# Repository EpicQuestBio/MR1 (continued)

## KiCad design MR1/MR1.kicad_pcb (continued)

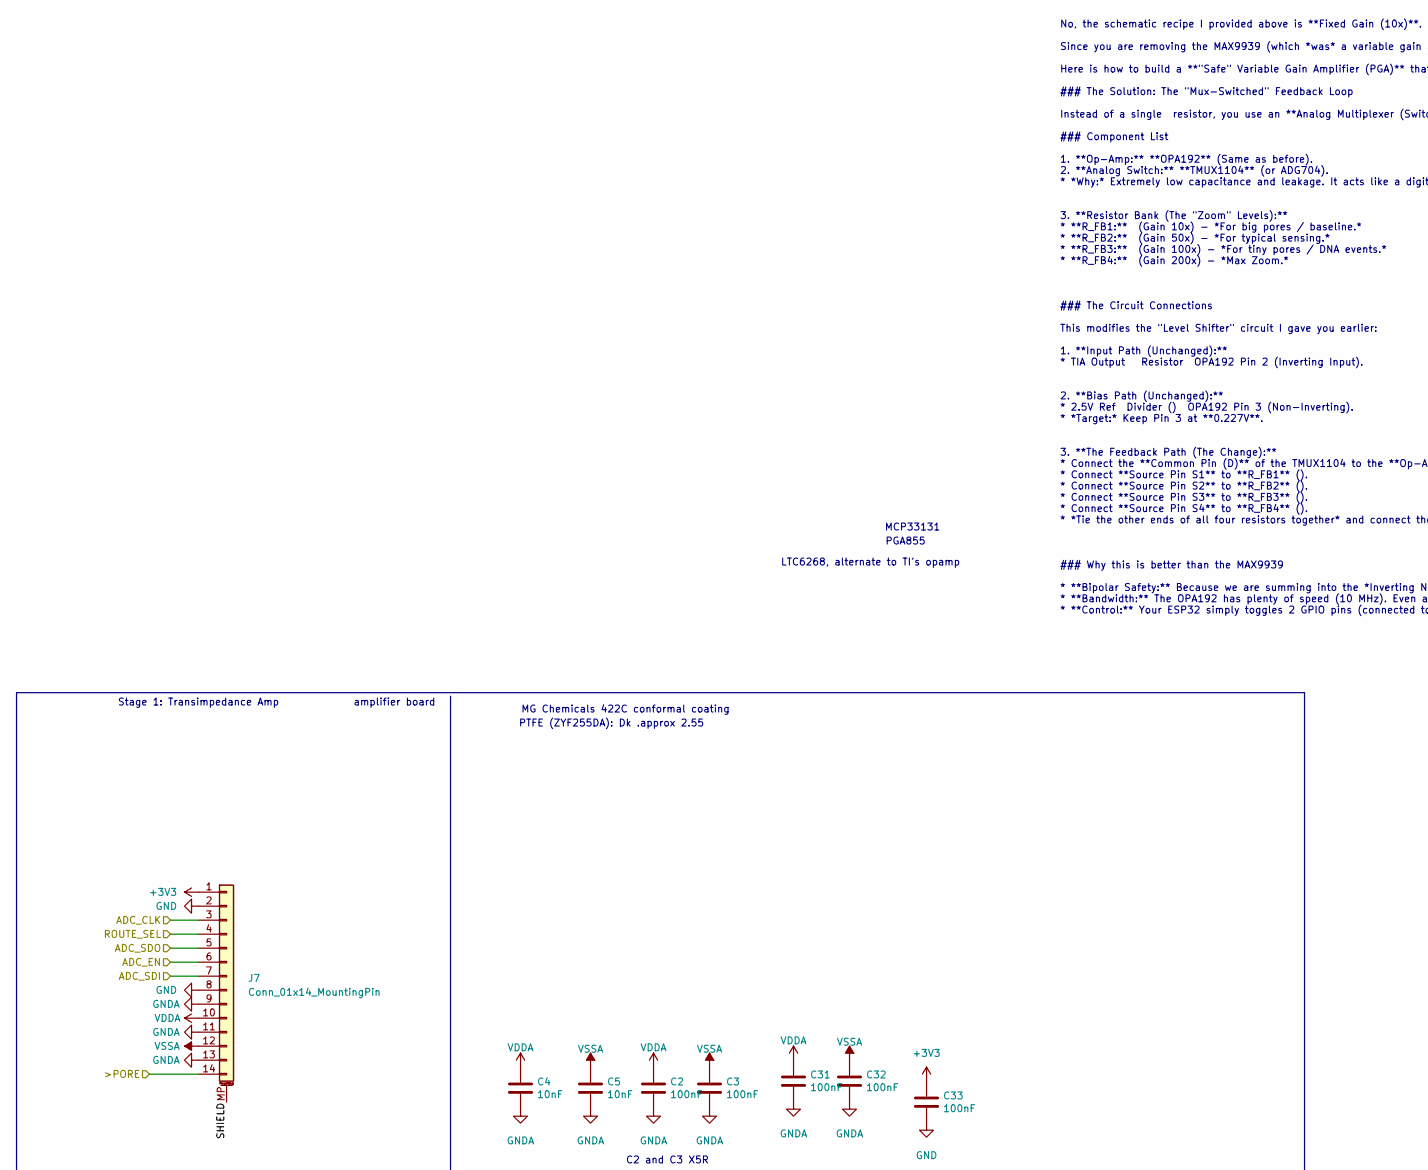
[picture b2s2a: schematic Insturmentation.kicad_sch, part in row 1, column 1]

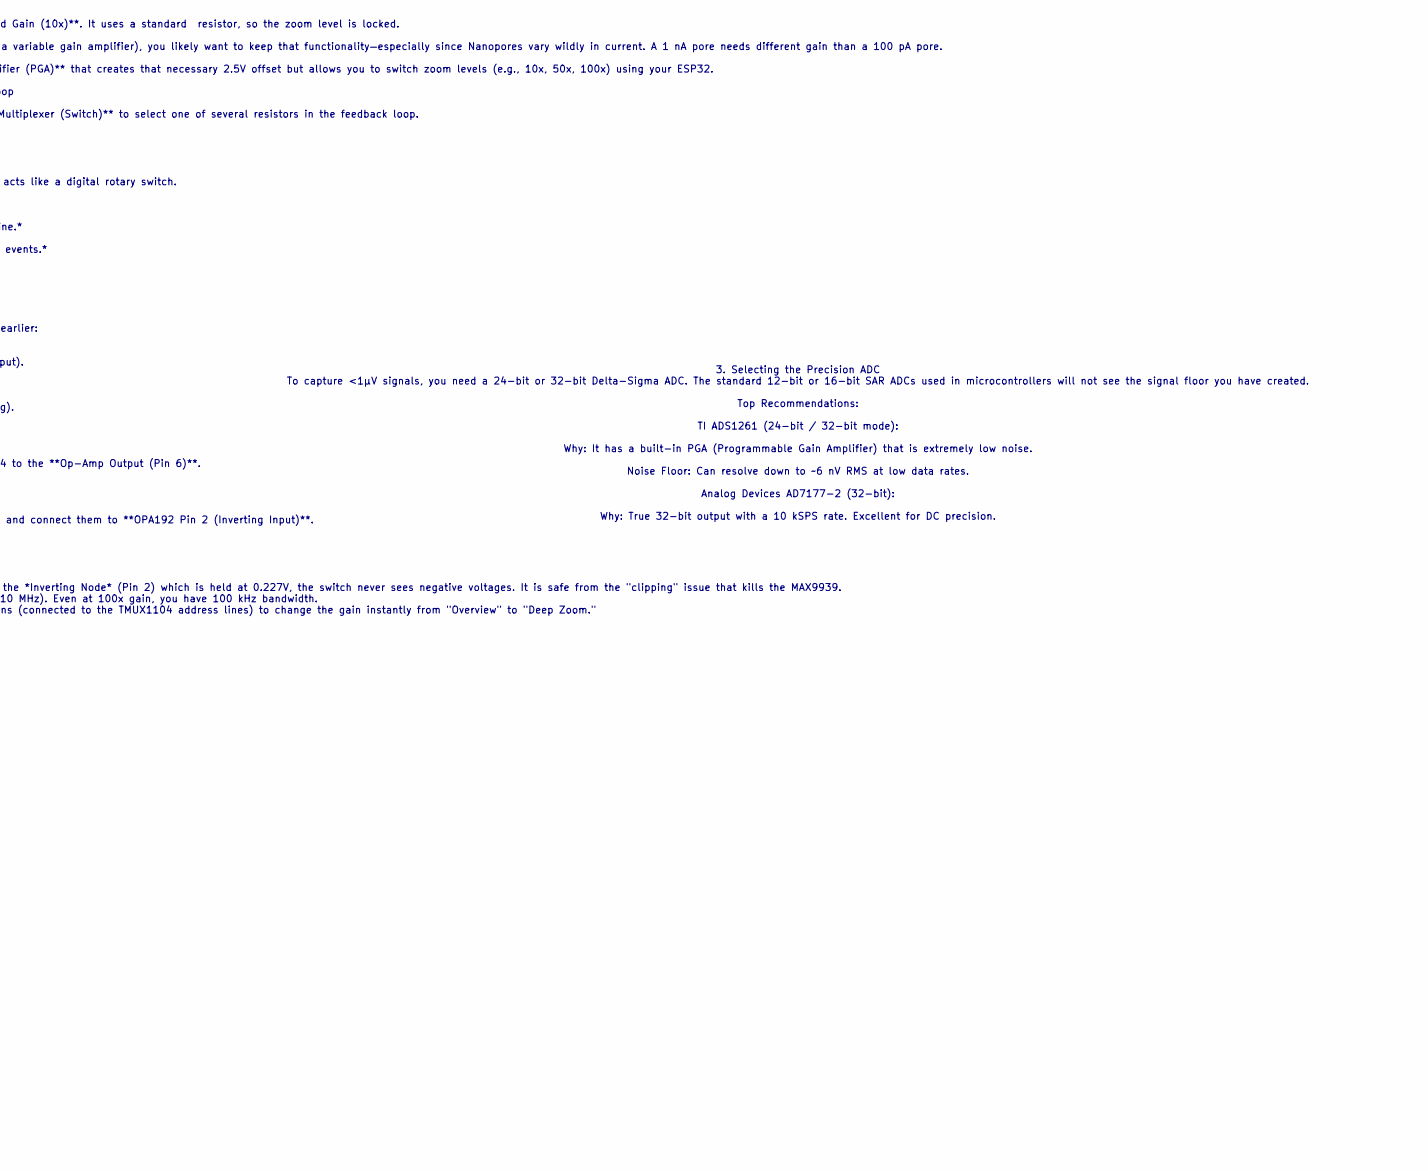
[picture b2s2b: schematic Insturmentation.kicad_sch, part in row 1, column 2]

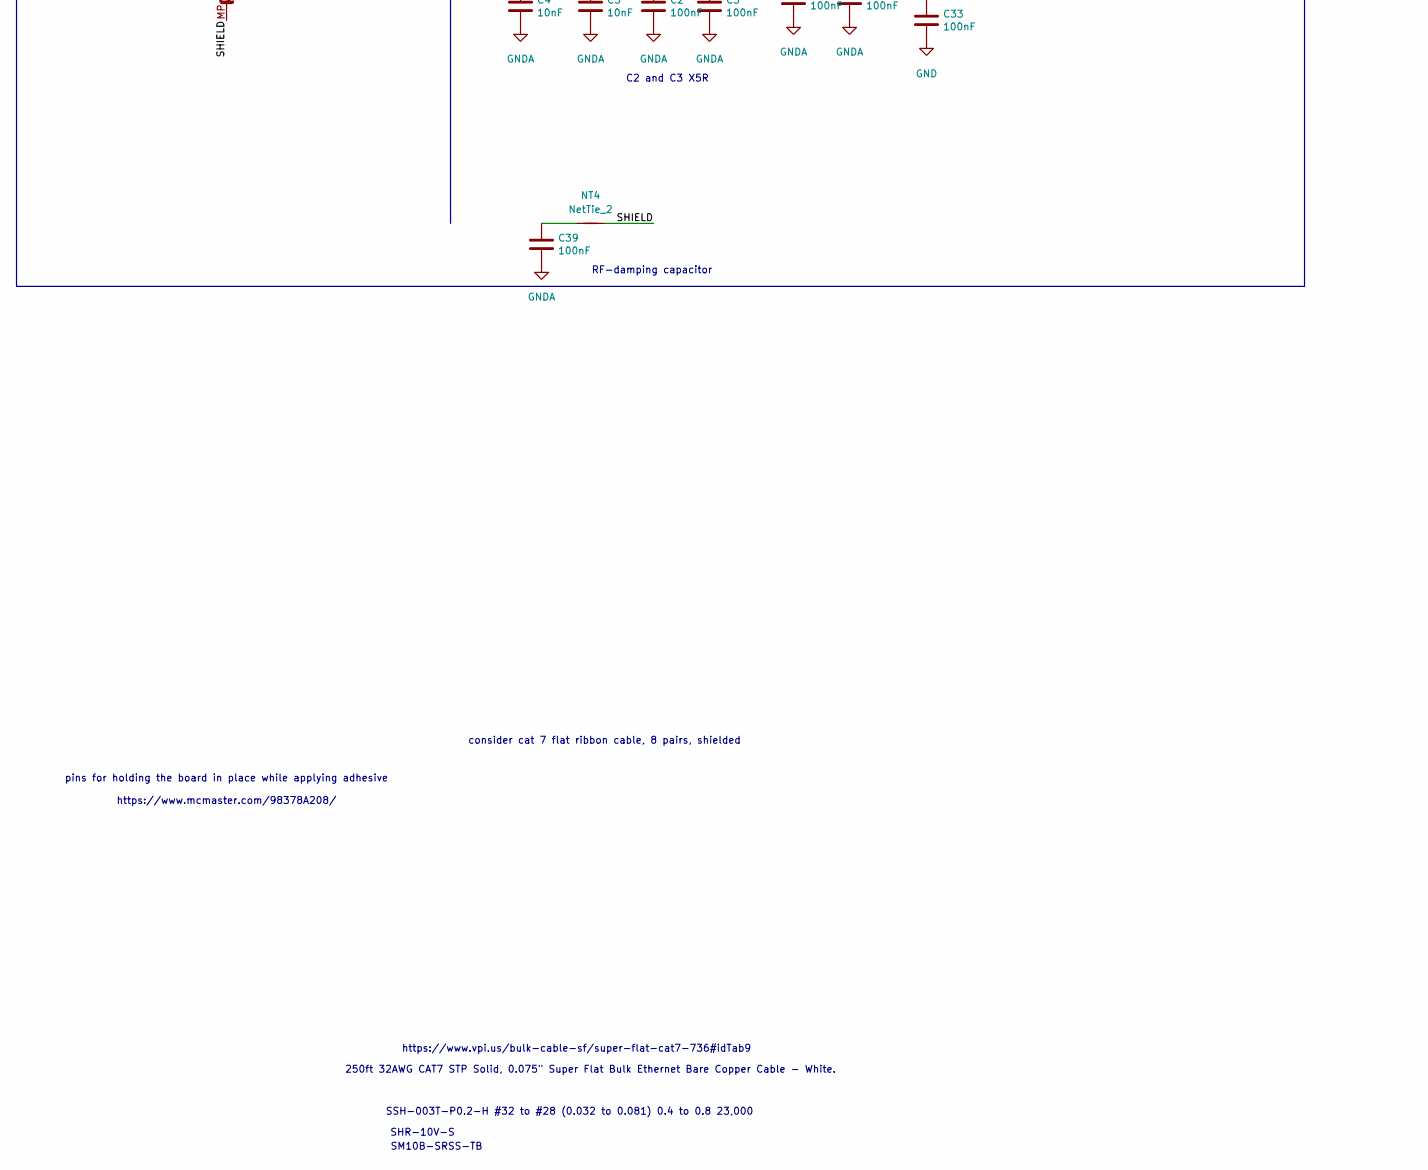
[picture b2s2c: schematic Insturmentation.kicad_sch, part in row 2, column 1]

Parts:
C2, C3, C31, C32, C33, C39: 100nF; C_0402_1005Metric; LCSC C15255
C4, C5: 10nF; C_0402_1005Metric; LCSC C1525
J7: Conn_01x14_MountingPin; Amphenol_F32R-1A7x1-11014_1x14-1MP_P0.5mm_Horizontal; LCSC C2856818
NT4: NetTie_2; NetTie-2_SMD_Pad0.5mm

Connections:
+3V3: C33.1, J7.1; also elsewhere on the board
/Ignition/>PORE: J7.14; also elsewhere on the board
/Insturmentation/ADC_CLK: J7.3; also elsewhere on the board
/Insturmentation/ADC_EN: J7.6; also elsewhere on the board
/Insturmentation/ADC_SDI: J7.7; also elsewhere on the board
/Insturmentation/ADC_SDO: J7.5; also elsewhere on the board
/Insturmentation/ROUTE_SEL: J7.4; also elsewhere on the board
/Insturmentation/SHIELD: J7.MP (MountPin), NT4.2
GND: C33.2, J7.2, J7.8; also elsewhere on the board
GNDA: C2.2, C3.2, C4.2, C5.2, C31.2, C32.2, C39.2, J7.9, J7.11, J7.13; also elsewhere on the board
unnamed: C39.1, NT4.1
VDDA: C2.1, C4.1, C31.1, J7.10; also elsewhere on the board
VSSA: C3.1, C5.1, C32.1, J7.12; also elsewhere on the board

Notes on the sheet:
consider cat 7 flat ribbon cable, 8 pairs, shielded
pins for holding the board in place while applying adhesive https://www.mcmaster.com/98378A208/
C2 and C3 X5R
PGA855
https://www.vpi.us/bulk-cable-sf/super-flat-cat7-736#idTab9
SM10B-SRSS-TB
PTFE (ZYF255DA): Dk .approx 2.55
amplifier board
No, the schematic recipe I provided above is **Fixed Gain (10x)**. It uses a standard resistor, so the zoom level is locked. Since you are removing the MAX9939 (which *was* a variable gain amplifier), you likely want to keep that functionality—especially since Nanopores vary wildly in current. A 1 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
Stage 1: Transimpedance Amp
MCP33131
MG Chemicals 422C conformal coating
250ft 32AWG CAT7 STP Solid, 0.075" Super Flat Bulk Ethernet Bare Copper Cable - White.
SHR-10V-S
LTC6268, alternate to TI's opamp
RF-damping capacitor
SSH-003T-P0.2-H #32 to #28 (0.032 to 0.081) 0.4 to 0.8 23,000
3. Selecting the Precision ADC To capture <1µV signals, you need a 24-bit or 32-bit Delta-Sigma ADC. The standard 12-bit or 16-bit SAR ADCs used in microcontrollers will not see the signal floor you have created. Top Recommendations: TI ADS1261 (24-bit / 32-bit mode): Why: It has a built-in PGA (Pr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

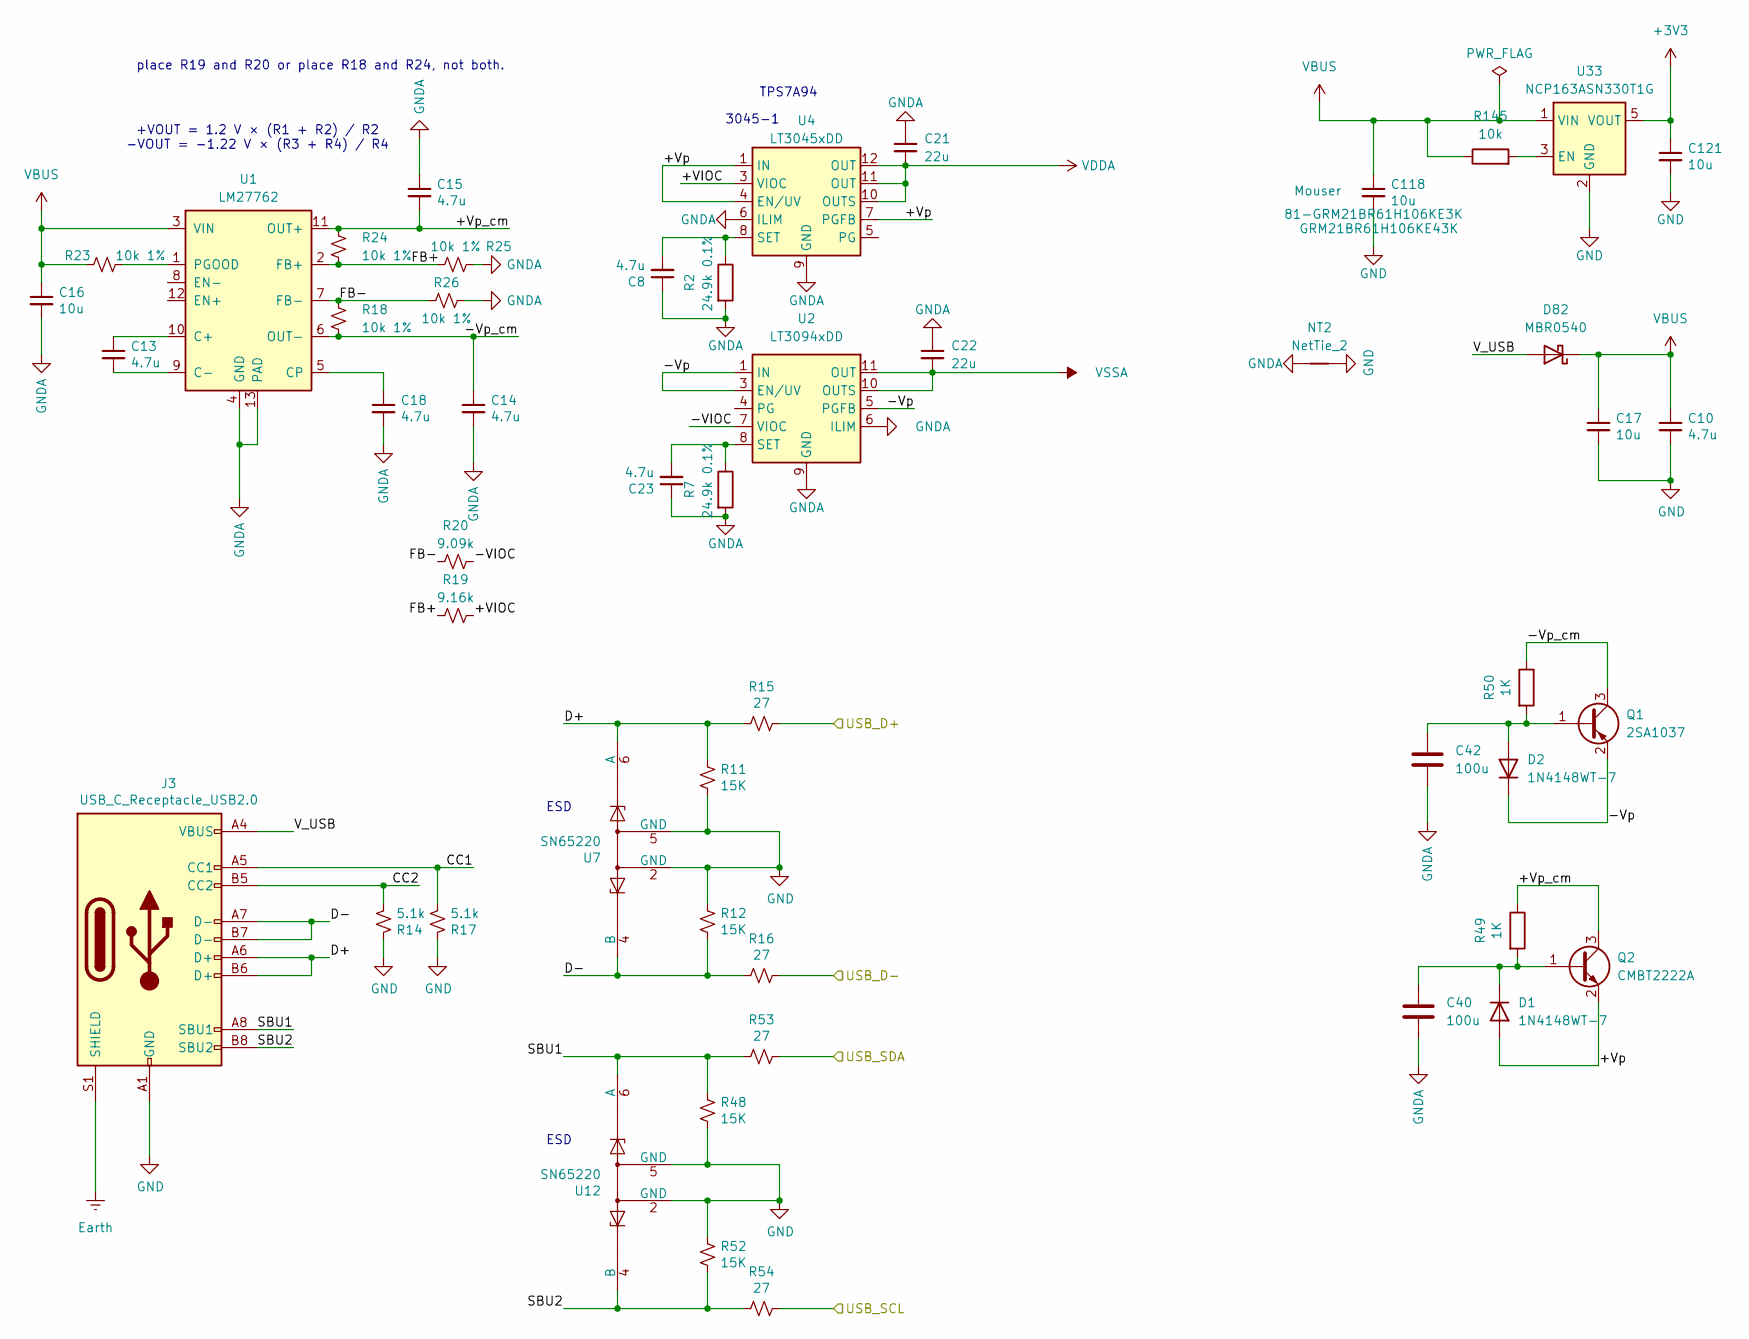
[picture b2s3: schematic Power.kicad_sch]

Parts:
C8, C10, C13, C14, C15, C18, C23: 4.7u; C_0402_1005Metric; Manufacturer_Part_Number JMK107C6475KA-T; LCSC C19702
C16, C17: 10u; C_0402_1005Metric; Manufacturer_Part_Number LMK212ABJ106MG-T; LCSC C1713
C21, C22: 22u; C_0402_1005Metric; MPN GRM21BR61H106KE43K; LCSC C23737
C40, C42: 100u; C_1206_3216Metric; LCSC C15008
C118, C121: 10u; C_0402_1005Metric; MPN GRM21BR61H106KE43K; LCSC C1713
D1, D2: 1N4148WT-7; D_SOD-523; LCSC C107849
D82: MBR0540; D_SOD-123; MPN MBR0540L-TP; LCSC C5204747
J3: USB_C_Receptacle_USB2.0; USB_C_Receptacle_HRO_TYPE-C-31-M-12; Manufacturer_Part_Number USB4105-GF-A; LCSC C165948
NT2: NetTie_2; NetTie-2_SMD_Pad0.5mm
Q1: 2SA1037; SOT-23; LCSC C14902
Q2: CMBT2222A; SOT-23; LCSC C2152
R2, R7: 24.9k 0.1%; R_0402_1005Metric; LCSC C25327
R11, R12, R48, R52: 15K; R_0402_1005Metric; Manufacturer_Part_Number RC0603FR-1315KL; LCSC C25275
R14, R17: 5.1k; R_0402_1005Metric; Manufacturer_Part_Number CR0603-FX-5101ELF; LCSC C25212
R15, R16, R53, R54: 27; R_0402_1005Metric; Manufacturer_Part_Number RK73B1JTTDD270J; LCSC C25078
R18, R23, R24, R25, R26: 10k 1%; R_0402_1005Metric; MPN RK73H1ETTPB1002F; LCSC C60490
R19: 9.16k; R_0402_1005Metric; MPN RK73H1ETTPB1002F; LCSC C25991
R20: 9.09k; R_0402_1005Metric; MPN RK73H1ETTPB1002F; LCSC C25879
R49, R50: 1K; R_0402_1005Metric; LCSC C25149
R145: 10k; R_0402_1005Metric; MPN RK73H1ETTPB1002F; LCSC C60490
U1: LM27762; WSON-12-1EP_3x2mm_P0.5mm_EP1x2.65_ThermalVias; MPN LM27762DSSR; LCSC C473398
U2: LT3094xDD; DFN-12-1EP_3x3mm_P0.45mm_EP1.65x2.38mm_ThermalVias; LCSC C670493
U4: LT3045xDD; DFN-12-1EP_3x3mm_P0.5mm_EP1.6x2.5mm; MPN LT3045EDD-1#TRPBF; LCSC C514420
U7, U12: SN65220; SOT-23-6; Manufacturer_Part_Number SN65220DBVT; LCSC C21787
U33: NCP163ASN330T1G; SOT-23-5; MPN NCP114ASN330T1G; LCSC C156285

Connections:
+3V3: C121.1, U33.5 (VOUT); also elsewhere on the board
/Microcontroller/GPIO19: R16.2; also elsewhere on the board
/Microcontroller/GPIO20: R15.2; also elsewhere on the board
/Microcontroller/GPIO21: R53.2; also elsewhere on the board
/Microcontroller/GPIO26: R54.2; also elsewhere on the board
/Power/+VIOC: R19.1, U4.3 (VIOC)
/Power/+Vp: D1.2 (A), Q2.2 (E), U4.1 (IN), U4.2 (IN), U4.4 (EN/UV), U4.7 (PGFB)
/Power/+Vp_cm: C15.2, Q2.3 (C), R24.2, R49.1, U1.11 (OUT+)
/Power/-VIOC: R20.1, U2.7 (VIOC)
/Power/-Vp: D2.1 (K), Q1.2 (E), U2.1 (IN), U2.2 (IN), U2.3 (EN/UV), U2.5 (PGFB), U2.13 (IN)
/Power/-Vp_cm: C14.1, Q1.3 (C), R18.1, R50.1, U1.6 (OUT-)
/Power/CC1: J3.A5 (CC1), R17.2
/Power/CC2: J3.B5 (CC2), R14.2
/Power/D+: J3.A6 (D+), J3.B6 (D+), R11.1, R15.1, U7.1, U7.6 (A)
/Power/D-: J3.A7 (D-), J3.B7 (D-), R12.2, R16.1, U7.3, U7.4 (B)
/Power/FB+: R19.2, R24.1, R25.2, U1.2 (FB+)
/Power/FB-: R18.2, R20.2, R26.1, U1.7 (FB-)
/Power/SBU1: J3.A8 (SBU1), R48.1, R53.1, U12.1, U12.6 (A)
/Power/SBU2: J3.B8 (SBU2), R52.2, R54.1, U12.3, U12.4 (B)
/Power/V_USB: D82.2 (A), J3.A4 (VBUS), J3.A9 (VBUS), J3.B4 (VBUS), J3.B9 (VBUS)
Earth: J3.S1 (SHIELD); also elsewhere on the board
GND: C10.2, C17.2, C118.2, C121.2, J3.A1 (GND), J3.A12 (GND), J3.B1 (GND), J3.B12 (GND), NT2.2, R11.2, R12.1, R14.1, R17.1, R48.2, R52.1, U7.2 (GND), U7.5 (GND), U12.2 (GND), U12.5 (GND), U33.2 (GND); also elsewhere on the board
GNDA: C8.1, C14.2, C15.1, C16.2, C18.2, C21.1, C22.1, C23.1, C40.2, C42.1, NT2.1, R2.2, R7.2, R25.1, R26.2, U1.4 (GND), U1.13 (PAD), U2.6 (ILIM), U2.9 (GND), U4.6 (ILIM), U4.9 (GND), U4.13 (GND); also elsewhere on the board
unnamed: C40.1, D1.1 (K), Q2.1 (B), R49.2
unnamed: C42.2, D2.2 (A), Q1.1 (B), R50.2
unnamed: C13.1, U1.10 (C+)
unnamed: C13.2, U1.9 (C-)
unnamed: C18.1, U1.5 (CP)
unnamed: R23.2, U1.1 (PGOOD)
unnamed: C23.2, R7.1, U2.8 (SET)
unnamed: C8.2, R2.1, U4.8 (SET)
unnamed: R145.2, U33.3 (EN)
VBUS: C10.1, C16.1, C17.1, C118.1, D82.1 (K), R23.1, R145.1, U1.3 (VIN), U33.1 (VIN)
VDDA: C21.2, U4.10 (OUTS), U4.11 (OUT), U4.12 (OUT); also elsewhere on the board
VSSA: C22.2, U2.10 (OUTS), U2.11 (OUT), U2.12 (OUT); also elsewhere on the board

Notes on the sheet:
ESD
+VOUT = 1.2 V × (R1 + R2) / R2 -VOUT = -1.22 V × (R3 + R4) / R4
3045-1
TPS7A94
place R19 and R20 or place R18 and R24, not both.

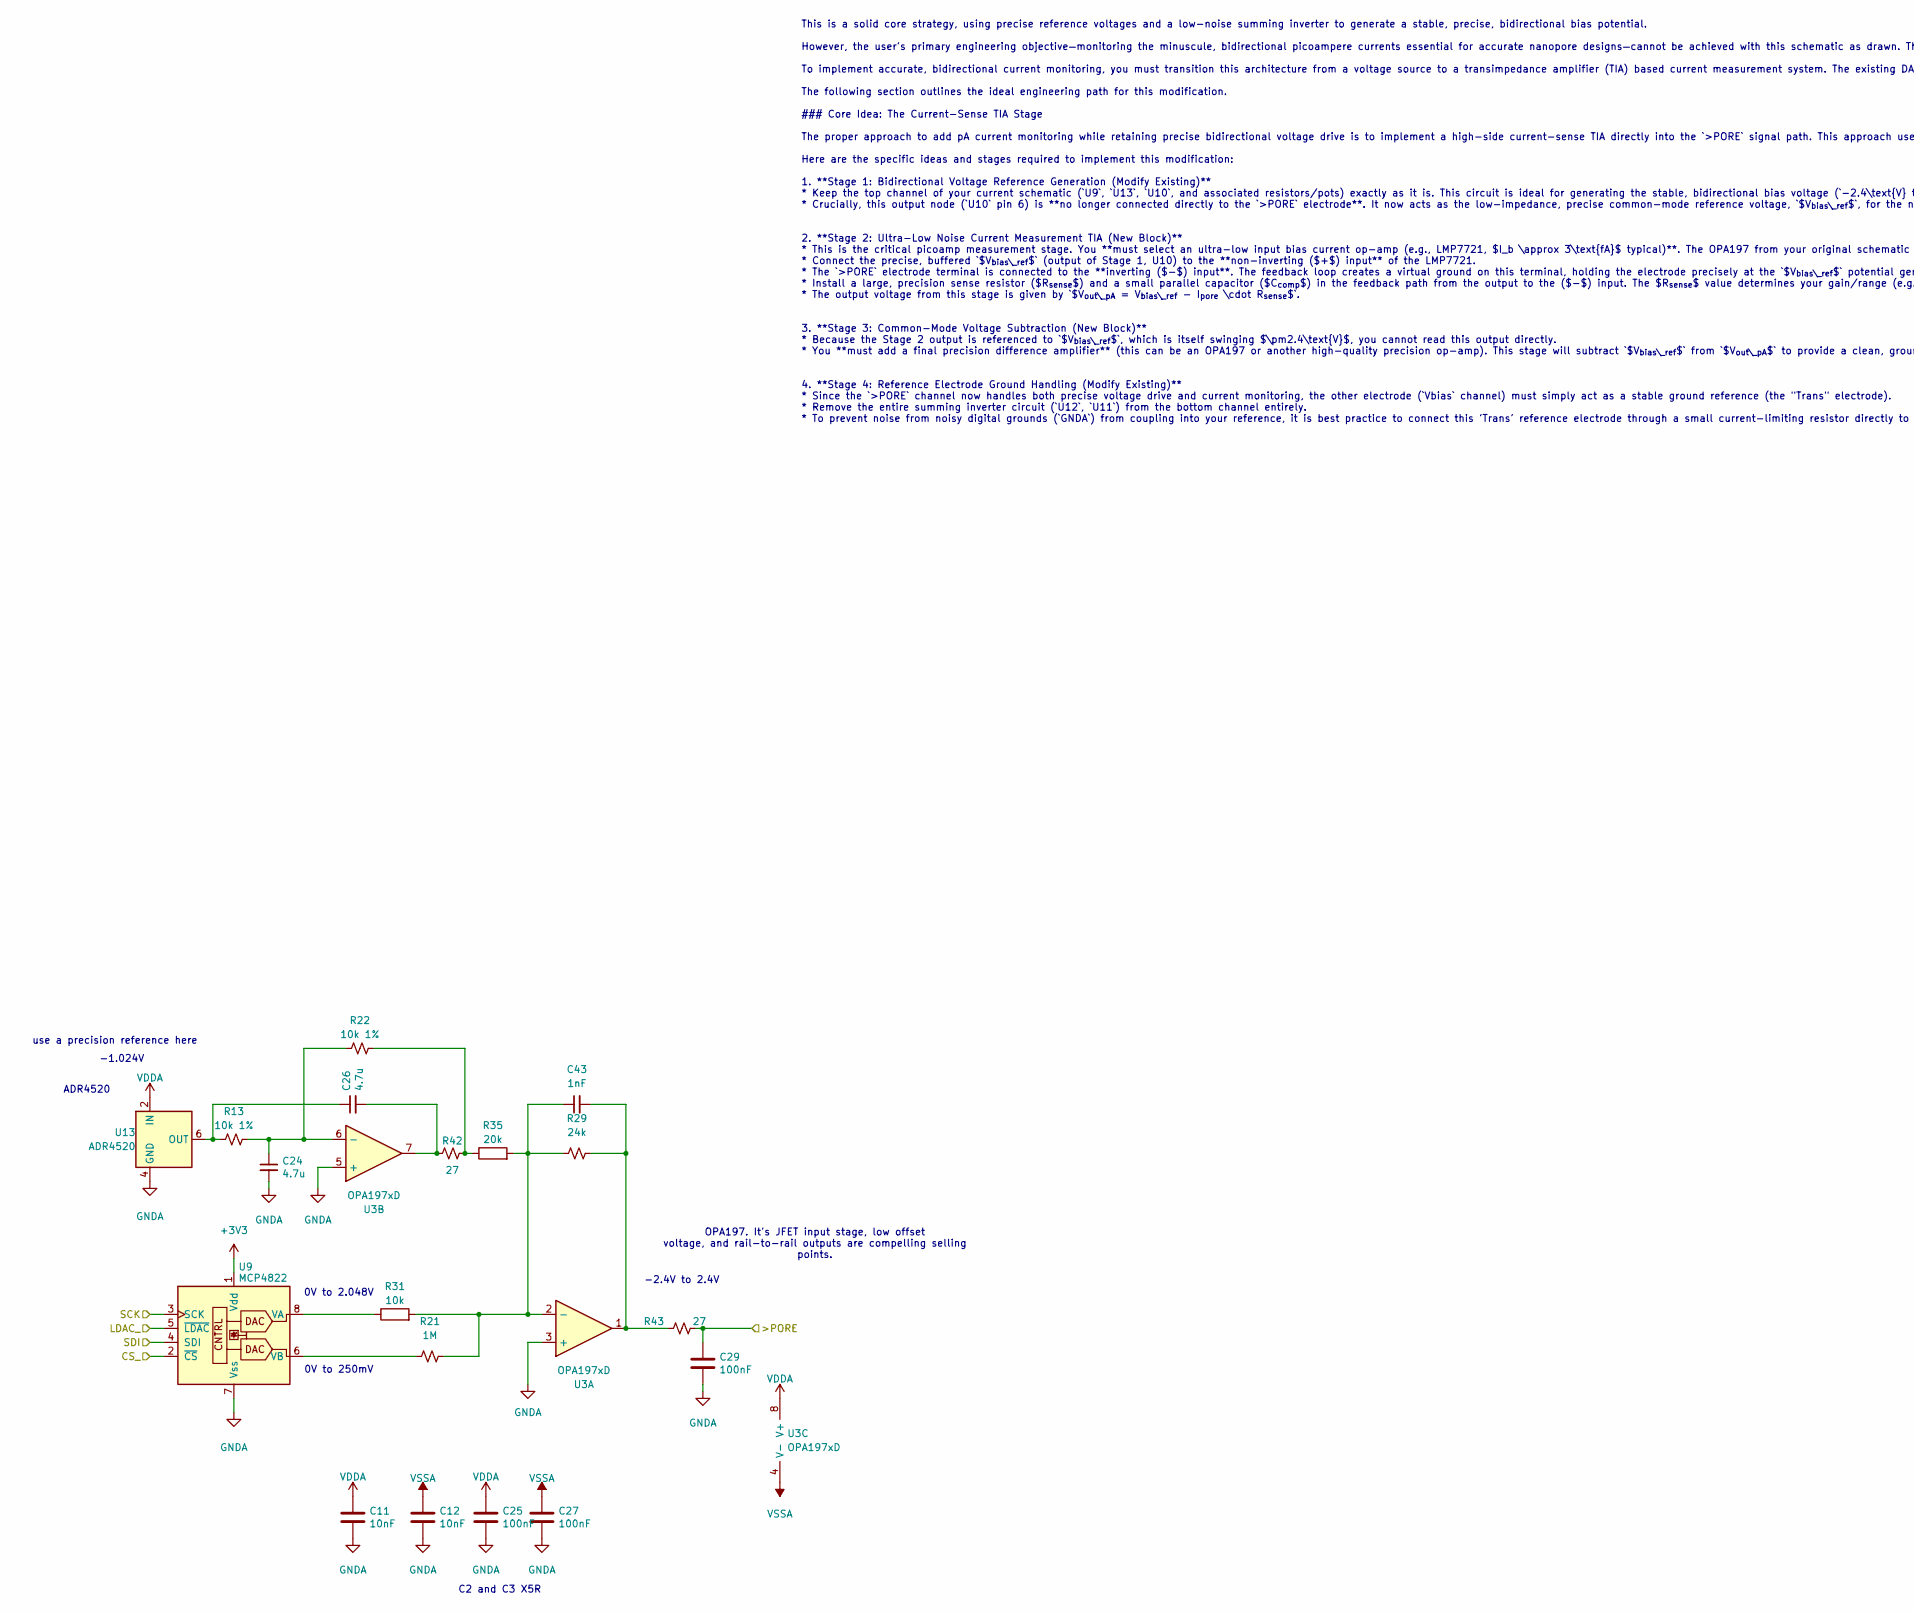
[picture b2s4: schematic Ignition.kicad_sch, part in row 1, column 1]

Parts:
C11, C12: 10nF; C_0402_1005Metric; LCSC C1525
C24, C26: 4.7u; C_0402_1005Metric; Manufacturer_Part_Number JMK107C6475KA-T; LCSC C19702
C25, C27, C29: 100nF; C_0402_1005Metric; LCSC C15255
C43: 1nF; C_0402_1005Metric; LCSC C1523
R13, R22: 10k 1%; R_0402_1005Metric; MPN RK73H1ETTPB1002F; LCSC C60490
R21: 1M; R_0402_1005Metric; MPN RK73H1ETTPB1002F; LCSC C25488
R29: 24k; R_0402_1005Metric; MPN RK73H1ETTPB1002F; LCSC C25324
R31: 10k; R_0402_1005Metric; LCSC C60490
R35: 20k; R_0402_1005Metric; LCSC C25310
R42, R43: 27; R_0402_1005Metric; MPN RC0402JR-0727RL; LCSC C25078
U3: OPA197xD; VSSOP-8_3x3mm_P0.65mm; MPN OPA197IDGKT; LCSC C133554
U9: MCP4822; SOIC-8-1EP_3.9x4.9mm_P1.27mm_EP2.29x3mm; MPN MCP4822T-E/SN; LCSC C16040
U13: ADR4520; SOIC-8_3.9x4.9mm_P1.27mm; MPN ADR4520ARZ-R7; LCSC C659578

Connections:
+3V3: U9.1 (Vdd); also elsewhere on the board
/Ignition/>PORE: C29.1, R43.2; also elsewhere on the board
/Ignition/CS_: U9.2 (~CS); also elsewhere on the board
/Ignition/LDAC_: U9.5 (~LDAC); also elsewhere on the board
/Ignition/SCK: U9.3 (SCK); also elsewhere on the board
/Ignition/SDI: U9.4 (SDI); also elsewhere on the board
GNDA: C11.2, C12.2, C24.2, C25.2, C27.2, C29.2, U3.3 (+), U3.5 (+), U9.7 (Vss), U13.4 (GND); also elsewhere on the board
unnamed: C26.2, R42.1, U3.7
unnamed: C43.2, R29.1, R43.1, U3.1
unnamed: R22.1, R35.1, R42.2
unnamed: C43.1, R21.1, R29.2, R31.2, R35.2, U3.2 (-)
unnamed: C24.1, R13.1, R22.2, U3.6 (-)
unnamed: R31.1, U9.8 (VA)
unnamed: R21.2, U9.6 (VB)
unnamed: C26.1, R13.2, U13.6 (OUT)
VDDA: C11.1, C25.1, U3.8 (V+), U13.2 (IN); also elsewhere on the board
VSSA: C12.1, C27.1, U3.4 (V-); also elsewhere on the board

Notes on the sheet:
use a precision reference here
This is a solid core strategy, using precise reference voltages and a low-noise summing inverter to generate a stable, precise, bidirectional bias potential. However, the user's primary engineering objective—monitoring the minuscule, bidirectional picoampere currents essential for accurate nanopore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
0V to 250mV
C2 and C3 X5R
-2.4V to 2.4V
OPA197. It's JFET input stage, low offset voltage, and rail-to-rail outputs are compelling selling points.
ADR4520
0V to 2.048V
-1.024V

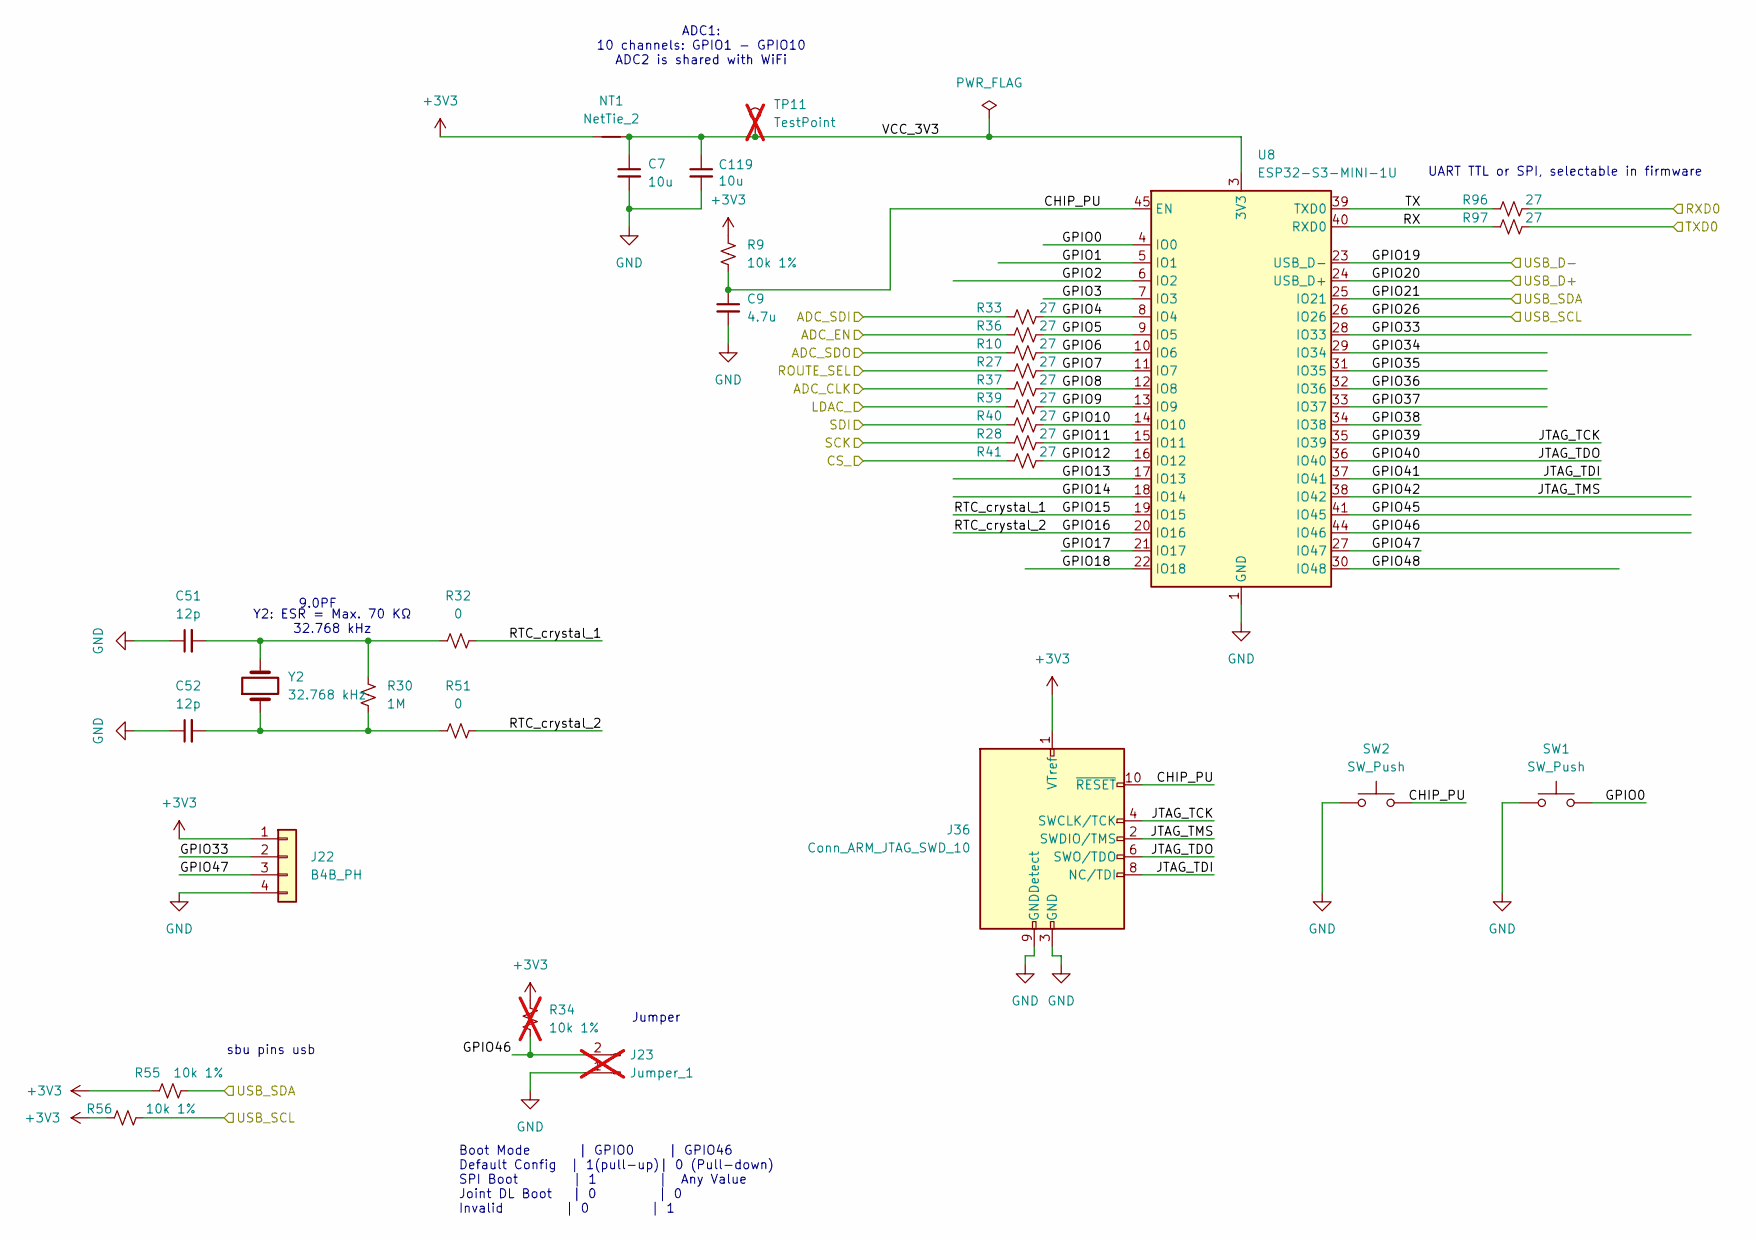
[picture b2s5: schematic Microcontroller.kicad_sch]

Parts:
C7, C119: 10u; C_0402_1005Metric; MPN GRM21BR61H106KE43K; LCSC C1713
C9: 4.7u; C_0402_1005Metric; MPN LMK107BJ475KA-T; LCSC C19702
C51, C52: 12p; C_0402_1005Metric; MPN 0402YA120JAT2A; LCSC C1550
J22: B4B_PH; JST_PH_B4B-PH-K_1x04_P2.00mm_Vertical; MPN B4B-PH-K-S; LCSC C131334
J23: Jumper_1; PinHeader_1x02_P2.54mm_Vertical; LCSC C492401; not fitted
J36: Conn_ARM_JTAG_SWD_10; PinHeader_2x05_P1.27mm_Vertical_SMD; MPN FTSH-105-01-F-DV-007-P-TR; LCSC C521634
NT1: NetTie_2; NetTie-2_SMD_Pad0.5mm
R9, R55, R56: 10k 1%; R_0402_1005Metric; MPN RK73H1ETTPB1002F; LCSC C60490
R10, R27, R28, R33, R36, R37, R39, R40, R41, R96, R97: 27; R_0402_1005Metric; MPN RC0402JR-0727RL; LCSC C25078
R30: 1M; R_0402_1005Metric; MPN CRCW04021M00DHEDP; LCSC C25488
R32, R51: 0; R_0402_1005Metric; MPN CRCW04020000Z0EDC; LCSC C25740
R34: 10k 1%; R_0402_1005Metric; MPN RK73H1ETTPB1002F; LCSC C60490; not fitted
SW1, SW2: SW_Push; SW_SPST_6mm_gull wing; MPN TS04-66-43-BK-160-SMT; LCSC C481177
TP11: TestPoint; TestPoint_Pad_D1.0mm; not fitted
U8: ESP32-S3-MINI-1U; ESP32-S2-MINI-1U; MPN ESP32-S3-MINI-1U-N8; LCSC C2980299
Y2: 32.768 kHz; Crystal_SMD_3215-2Pin_3.2x1.5mm; MPN FC3215AN 32.768K-90NN60KC5; LCSC C91275

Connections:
+3V3: J22.1, J36.1 (VTref), NT1.1, R9.1, R34.1, R55.1, R56.2; also elsewhere on the board
/Ignition/CS_: R41.1; also elsewhere on the board
/Ignition/LDAC_: R39.1; also elsewhere on the board
/Ignition/SCK: R28.1; also elsewhere on the board
/Ignition/SDI: R40.1; also elsewhere on the board
/Insturmentation/ADC_CLK: R37.1; also elsewhere on the board
/Insturmentation/ADC_EN: R36.1; also elsewhere on the board
/Insturmentation/ADC_SDI: R33.1; also elsewhere on the board
/Insturmentation/ADC_SDO: R10.1; also elsewhere on the board
/Insturmentation/ROUTE_SEL: R27.1; also elsewhere on the board
/Microcontroller/CHIP_PU: C9.1, J36.10 (~RESET), R9.2, SW2.2, U8.45 (EN)
/Microcontroller/GPIO0: SW1.2, U8.4 (IO0)
/Microcontroller/GPIO1: U8.5 (IO1)
/Microcontroller/GPIO2: U8.6 (IO2)
/Microcontroller/GPIO3: U8.7 (IO3)
/Microcontroller/GPIO4: R33.2, U8.8 (IO4)
/Microcontroller/GPIO5: R36.2, U8.9 (IO5)
/Microcontroller/GPIO6: R10.2, U8.10 (IO6)
/Microcontroller/GPIO7: R27.2, U8.11 (IO7)
/Microcontroller/GPIO8: R37.2, U8.12 (IO8)
/Microcontroller/GPIO9: R39.2, U8.13 (IO9)
/Microcontroller/GPIO10: R40.2, U8.14 (IO10)
/Microcontroller/GPIO11: R28.2, U8.15 (IO11)
/Microcontroller/GPIO12: R41.2, U8.16 (IO12)
/Microcontroller/GPIO13: U8.17 (IO13)
/Microcontroller/GPIO14: U8.18 (IO14)
/Microcontroller/GPIO15: R32.2, U8.19 (IO15)
/Microcontroller/GPIO16: R51.1, U8.20 (IO16)
/Microcontroller/GPIO17: U8.21 (IO17)
/Microcontroller/GPIO18: U8.22 (IO18)
/Microcontroller/GPIO19: U8.23 (USB_D-); also elsewhere on the board
/Microcontroller/GPIO20: U8.24 (USB_D+); also elsewhere on the board
/Microcontroller/GPIO21: R55.2, U8.25 (IO21); also elsewhere on the board
/Microcontroller/GPIO26: R56.1, U8.26 (IO26); also elsewhere on the board
/Microcontroller/GPIO33: J22.2, U8.28 (IO33)
/Microcontroller/GPIO34: U8.29 (IO34)
/Microcontroller/GPIO35: U8.31 (IO35)
/Microcontroller/GPIO36: U8.32 (IO36)
/Microcontroller/GPIO37: U8.33 (IO37)
/Microcontroller/GPIO38: U8.34 (IO38)
/Microcontroller/GPIO39: J36.4 (SWCLK/TCK), U8.35 (IO39)
/Microcontroller/GPIO40: J36.6 (SWO/TDO), U8.36 (IO40)
/Microcontroller/GPIO41: J36.8 (NC/TDI), U8.37 (IO41)
/Microcontroller/GPIO42: J36.2 (SWDIO/TMS), U8.38 (IO42)
/Microcontroller/GPIO45: U8.41 (IO45)
/Microcontroller/GPIO46: J23.2, R34.2, U8.44 (IO46)
/Microcontroller/GPIO47: J22.3, U8.27 (IO47)
/Microcontroller/GPIO48: U8.30 (IO48)
/Microcontroller/RX: R97.1, U8.40 (RXD0)
/Microcontroller/RXD0: R96.2
/Microcontroller/TX: R96.1, U8.39 (TXD0)
/Microcontroller/TXD0: R97.2
/Microcontroller/VCC_3V3: C7.1, C119.1, NT1.2, TP11.1 (1_1), U8.3 (3V3)
GND: C7.2, C9.2, C51.1, C52.1, C119.2, J22.4, J23.1, J36.3 (GND), J36.5 (GND), J36.9 (GNDDetect), SW1.1, SW2.1, U8.1 (GND), U8.2 (GND), U8.42 (GND), U8.43 (GND), U8.46 (GND), U8.47 (GND), U8.48 (GND), U8.49 (GND), U8.50 (GND), U8.51 (GND), U8.52 (GND), U8.53 (GND), U8.54 (GND), U8.55 (GND), U8.56 (GND), U8.57 (GND), U8.58 (GND), U8.59 (GND), U8.60 (GND), U8.61 (GND), U8.62 (GND), U8.63 (GND), U8.64 (GND), U8.65 (GND); also elsewhere on the board
unnamed: C51.2, R30.1, R32.1, Y2.2
unnamed: C52.2, R30.2, R51.2, Y2.1

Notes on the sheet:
Jumper
9.0PF
UART TTL or SPI, selectable in firmware
Boot Mode | GPIO0 | GPIO46 Default Config | 1(pull-up)| 0 (Pull-down) SPI Boot | 1 | Any Value Joint DL Boot | 0 | 0 Invalid | 0 | 1
Y2: ESR = Max. 70 KΩ 32.768 kHz
sbu pins usb
ADC1: 10 channels: GPIO1 - GPIO10 ADC2 is shared with WiFi

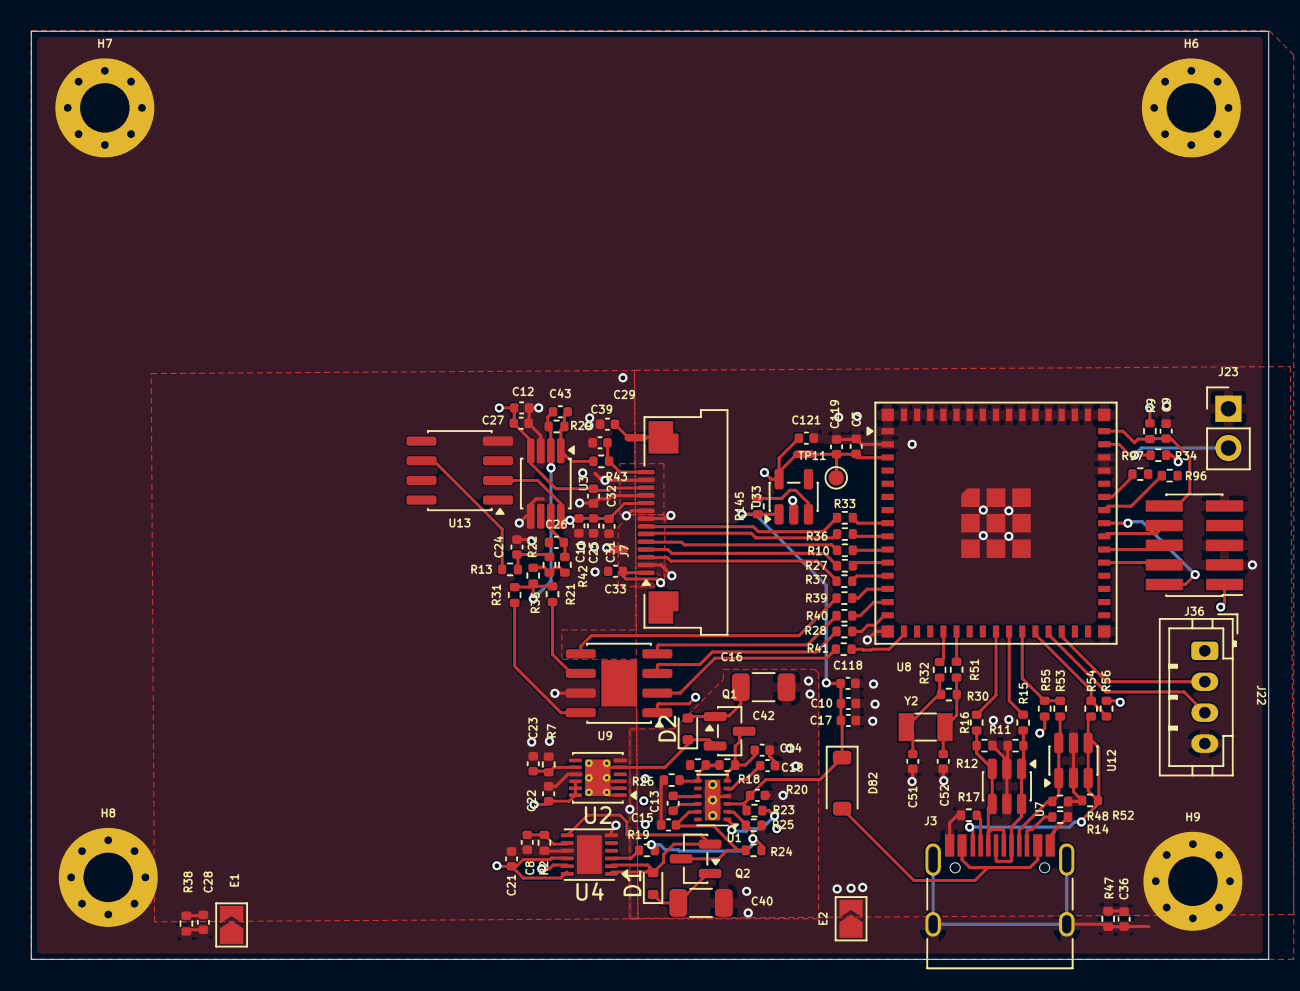
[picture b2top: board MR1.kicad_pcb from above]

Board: 4 copper layers, 80.0 x 60.0 mm, 113 parts (0 on the bottom side), 79 nets.
